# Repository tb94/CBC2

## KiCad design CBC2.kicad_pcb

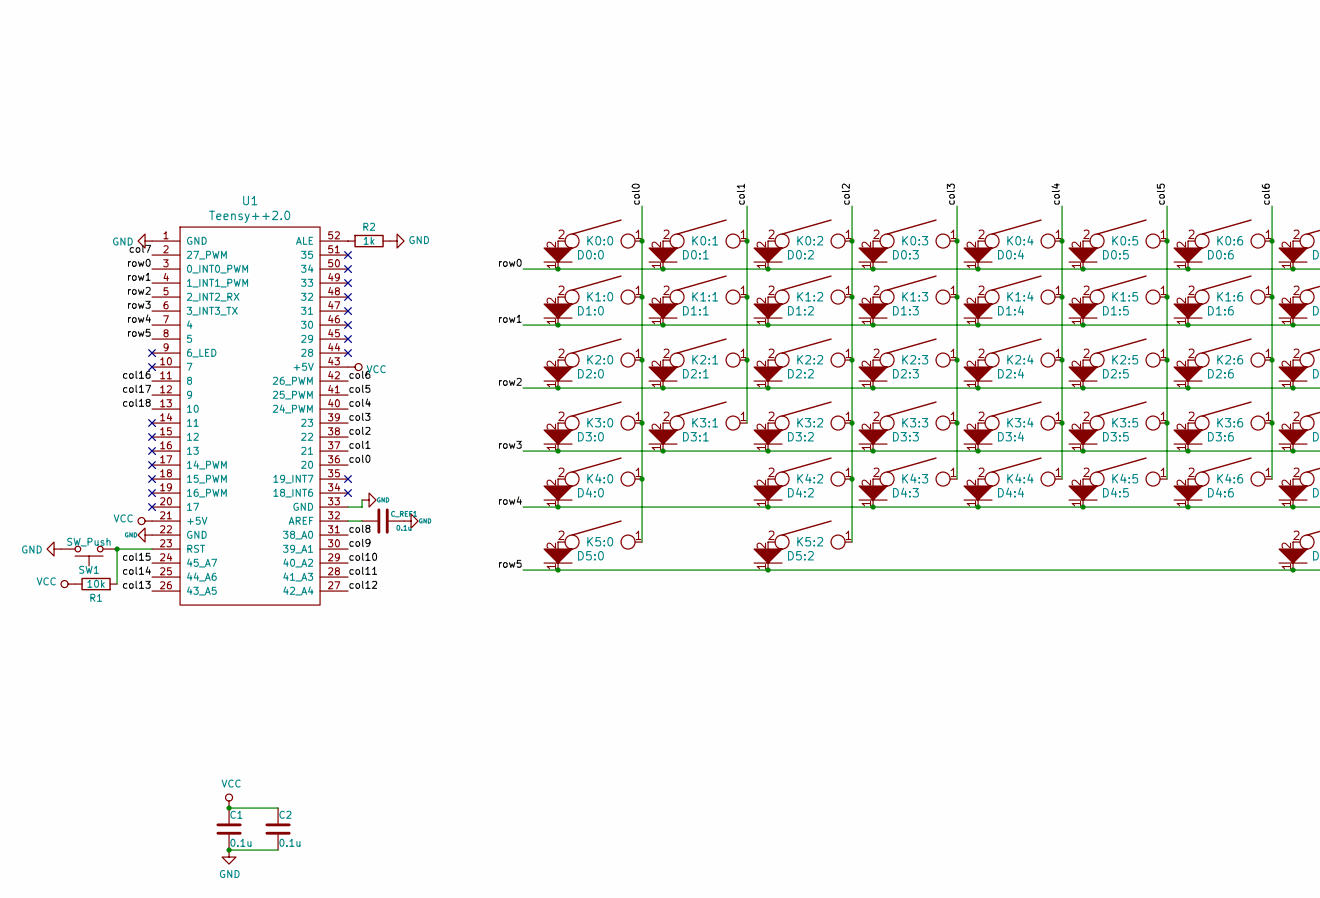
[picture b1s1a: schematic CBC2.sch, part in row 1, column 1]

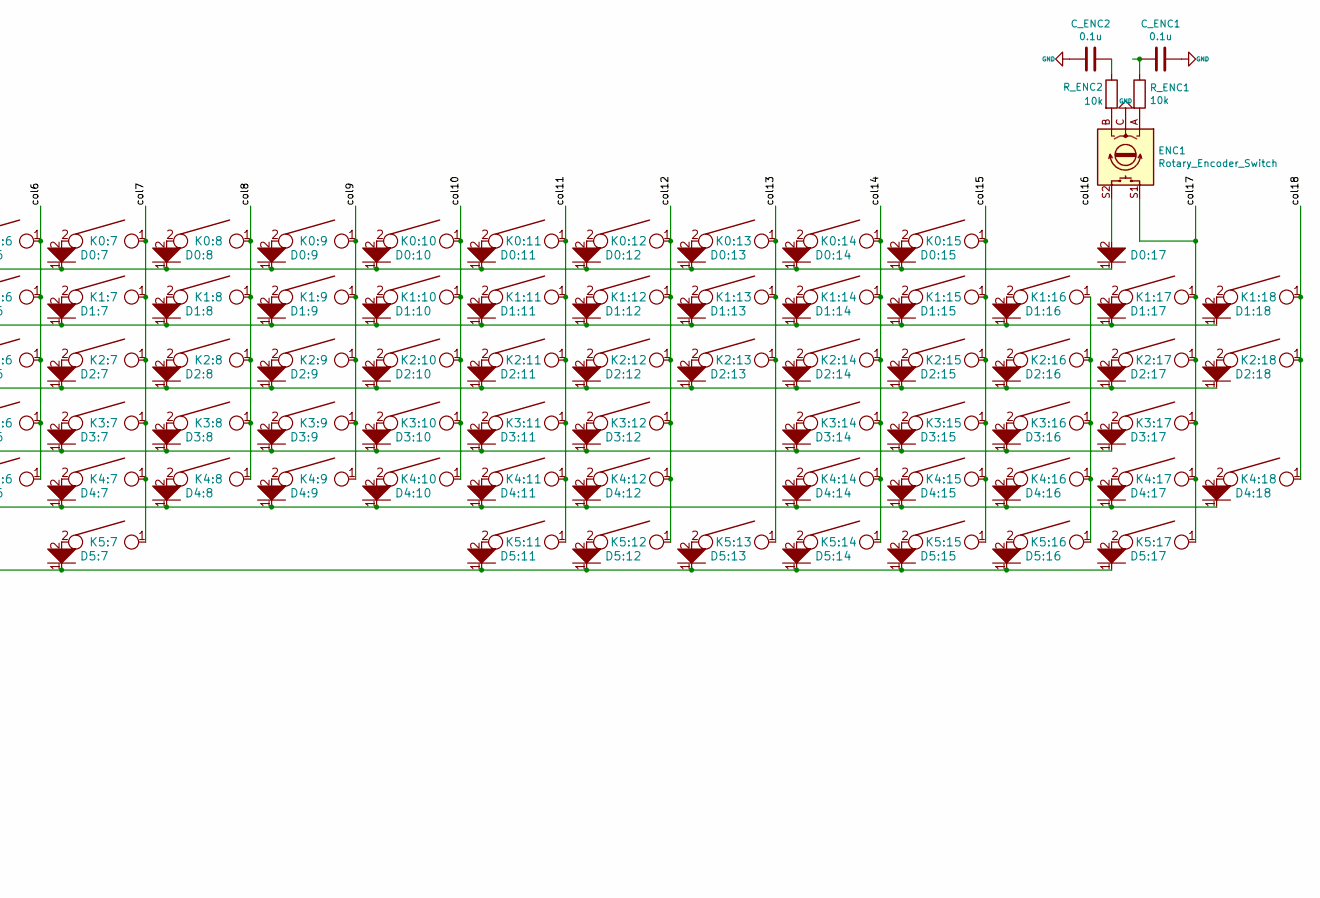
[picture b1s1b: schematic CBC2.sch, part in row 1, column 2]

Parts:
C1, C2: 0.1u; C_Axial_L3.8mm_D2.6mm_P7.50mm_Horizontal
C_ENC1, C_ENC2: 0.1u; C_Axial_L3.8mm_D2.6mm_P7.50mm_Horizontal
C_REF1: 0.1u; C_Axial_L3.8mm_D2.6mm_P7.50mm_Horizontal
D0:0, D0:1, D0:2, D0:3, D0:4, D0:5, D0:6, D0:7, D0:8, D0:9, D0:10, D0:11, D0:12, D0:13, D0:14, D0:15, D0:17, D1:0, D1:1, D1:2, D1:3, D1:4, D1:5, D1:6, D1:7, D1:8, D1:9, D1:10, D1:11, D1:12, D1:13, D1:14, D1:15, D1:16, D1:17, D1:18, D2:0, D2:1, D2:2, D2:3, D2:4, D2:5, D2:6, D2:7, D2:8, D2:9, D2:10, D2:11, D2:12, D2:13, D2:14, D2:15, D2:16, D2:17, D2:18, D3:0, D3:1, D3:2, D3:3, D3:4, D3:5, D3:6, D3:7, D3:8, D3:9, D3:10, D3:11, D3:12, D3:14, D3:15, D3:16, D3:17, D4:0, D4:2, D4:3, D4:4, D4:5, D4:6, D4:7, D4:8, D4:9, D4:10, D4:11, D4:12, D4:14, D4:15, D4:16, D4:17, D4:18, D5:0, D5:2, D5:7, D5:11, D5:12, D5:13, D5:14, D5:15, D5:16, D5:17: D; Diode-dual
ENC1: Rotary_Encoder_Switch; RotaryEncoder_Alps_EC11E-Switch_Vertical_H20mm
K0:0, K0:1, K0:2, K0:3, K0:4, K0:5, K0:6, K0:7, K0:8, K0:9, K0:10, K0:11, K0:12, K0:13, K0:14, K0:15, K1:0, K1:1, K1:2, K1:3, K1:4, K1:5, K1:6, K1:7, K1:8, K1:9, K1:10, K1:11, K1:12, K1:14, K1:15, K1:16, K1:17, K1:18, K2:1, K2:2, K2:3, K2:4, K2:5, K2:6, K2:7, K2:8, K2:9, K2:10, K2:11, K2:12, K2:14, K2:15, K2:16, K2:17, K3:1, K3:2, K3:3, K3:4, K3:5, K3:6, K3:7, K3:8, K3:9, K3:10, K3:11, K3:14, K3:15, K3:16, K3:17, K4:2, K4:3, K4:4, K4:5, K4:6, K4:7, K4:8, K4:9, K4:10, K4:11, K4:14, K4:15, K4:16, K4:17, K5:13, K5:14, K5:15, K5:16, K5:17: KEYSW; MX-1U
K1:13, K2:18, K4:18: KEYSW; MX-2U
K2:0, K2:13, K5:0, K5:2, K5:11, K5:12: KEYSW; MX-1.5U
K3:0: KEYSW; MX-1.75U
K3:12, K4:0: KEYSW; MX-2.25U
K4:12: KEYSW; MX-2.75U
K5:7: KEYSW; MX-7U
R1: 10k; R_Axial_DIN0204_L3.6mm_D1.6mm_P5.08mm_Horizontal
R2: 1k; R_Axial_DIN0204_L3.6mm_D1.6mm_P5.08mm_Horizontal
R_ENC1, R_ENC2: 10k; R_Axial_DIN0204_L3.6mm_D1.6mm_P5.08mm_Horizontal
SW1: SW_Push; SW_Tactile_SPST_Angled_MJTP1117
U1: Teensy++2.0; Teensy2.0++

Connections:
/col0: K0:0.1, K1:0.1, K2:0.1, K3:0.1, K4:0.1, K5:0.1, U1.36 (20)
/col1: K0:1.1, K1:1.1, K2:1.1, K3:1.1, U1.37 (21)
/col2: K0:2.1, K1:2.1, K2:2.1, K3:2.1, K4:2.1, K5:2.1, U1.38 (22)
/col3: K0:3.1, K1:3.1, K2:3.1, K3:3.1, K4:3.1, U1.39 (23)
/col4: K0:4.1, K1:4.1, K2:4.1, K3:4.1, K4:4.1, U1.40 (24_PWM)
/col5: K0:5.1, K1:5.1, K2:5.1, K3:5.1, K4:5.1, U1.41 (25_PWM)
/col6: K0:6.1, K1:6.1, K2:6.1, K3:6.1, K4:6.1, U1.42 (26_PWM)
/col7: K0:7.1, K1:7.1, K2:7.1, K3:7.1, K4:7.1, K5:7.1, U1.2 (27_PWM)
/col8: K0:8.1, K1:8.1, K2:8.1, K3:8.1, K4:8.1, U1.31 (38_A0)
/col9: K0:9.1, K1:9.1, K2:9.1, K3:9.1, K4:9.1, U1.30 (39_A1)
/col10: K0:10.1, K1:10.1, K2:10.1, K3:10.1, K4:10.1, U1.29 (40_A2)
/col11: K0:11.1, K1:11.1, K2:11.1, K3:11.1, K4:11.1, K5:11.1, U1.28 (41_A3)
/col12: K0:12.1, K1:12.1, K2:12.1, K3:12.1, K4:12.1, K5:12.1, U1.27 (42_A4)
/col13: K0:13.1, K1:13.1, K2:13.1, K5:13.1, U1.26 (43_A5)
/col14: K0:14.1, K1:14.1, K2:14.1, K3:14.1, K4:14.1, K5:14.1, U1.25 (44_A6)
/col15: K0:15.1, K1:15.1, K2:15.1, K3:15.1, K4:15.1, K5:15.1, U1.24 (45_A7)
/col16: U1.11 (8)
/col17: ENC1.S1, K1:17.1, K2:17.1, K3:17.1, K4:17.1, K5:17.1, U1.12 (9)
/col18: K1:18.1, K2:18.1, K4:18.1, U1.13 (10)
/row0: D0:0.1, D0:1.1, D0:2.1, D0:3.1, D0:4.1, D0:5.1, D0:6.1, D0:7.1, D0:8.1, D0:9.1, D0:10.1, D0:11.1, D0:12.1, D0:13.1, D0:14.1, D0:15.1, D0:17.1, U1.3 (0_INT0_PWM)
/row1: D1:0.1, D1:1.1, D1:2.1, D1:3.1, D1:4.1, D1:5.1, D1:6.1, D1:7.1, D1:8.1, D1:9.1, D1:10.1, D1:11.1, D1:12.1, D1:13.1, D1:14.1, D1:15.1, D1:16.1, D1:17.1, D1:18.1, U1.4 (1_INT1_PWM)
/row2: D2:0.1, D2:1.1, D2:2.1, D2:3.1, D2:4.1, D2:5.1, D2:6.1, D2:7.1, D2:8.1, D2:9.1, D2:10.1, D2:11.1, D2:12.1, D2:13.1, D2:14.1, D2:15.1, D2:16.1, D2:17.1, D2:18.1, U1.5 (2_INT2_RX)
/row3: D3:0.1, D3:1.1, D3:2.1, D3:3.1, D3:4.1, D3:5.1, D3:6.1, D3:7.1, D3:8.1, D3:9.1, D3:10.1, D3:11.1, D3:12.1, D3:14.1, D3:15.1, D3:16.1, D3:17.1, U1.6 (3_INT3_TX)
/row4: D4:0.1, D4:2.1, D4:3.1, D4:4.1, D4:5.1, D4:6.1, D4:7.1, D4:8.1, D4:9.1, D4:10.1, D4:11.1, D4:12.1, D4:14.1, D4:15.1, D4:16.1, D4:17.1, D4:18.1, U1.7 (4)
/row5: D5:0.1, D5:2.1, D5:7.1, D5:11.1, D5:12.1, D5:13.1, D5:14.1, D5:15.1, D5:16.1, D5:17.1, U1.8 (5)
GND: C1.2, C2.2, C_ENC1.1, C_ENC2.2, C_REF1.1, ENC1.C, R2.1, SW1.2, U1.1 (GND), U1.22 (GND), U1.33 (GND)
unnamed: C_ENC1.2, R_ENC1.1
unnamed: C_ENC2.1, R_ENC2.1
unnamed: C_REF1.2, U1.32 (AREF)
unnamed: D0:0.2, K0:0.2
unnamed: D0:1.2, K0:1.2
unnamed: D0:2.2, K0:2.2
unnamed: D0:3.2, K0:3.2
unnamed: D0:4.2, K0:4.2
unnamed: D0:5.2, K0:5.2
unnamed: D0:6.2, K0:6.2
unnamed: D0:7.2, K0:7.2
unnamed: D0:8.2, K0:8.2
unnamed: D0:9.2, K0:9.2
unnamed: D0:10.2, K0:10.2
unnamed: D0:11.2, K0:11.2
unnamed: D0:12.2, K0:12.2
unnamed: D0:13.2, K0:13.2
unnamed: D0:14.2, K0:14.2
unnamed: D0:15.2, K0:15.2
unnamed: D0:17.2, ENC1.S2
unnamed: D1:0.2, K1:0.2
unnamed: D1:1.2, K1:1.2
unnamed: D1:2.2, K1:2.2
unnamed: D1:3.2, K1:3.2
unnamed: D1:4.2, K1:4.2
unnamed: D1:5.2, K1:5.2
unnamed: D1:6.2, K1:6.2
unnamed: D1:7.2, K1:7.2
unnamed: D1:8.2, K1:8.2
unnamed: D1:9.2, K1:9.2
unnamed: D1:10.2, K1:10.2
unnamed: D1:11.2, K1:11.2
unnamed: D1:12.2, K1:12.2
unnamed: D1:13.2, K1:13.2
unnamed: D1:14.2, K1:14.2
unnamed: D1:15.2, K1:15.2
unnamed: D1:16.2, K1:16.2
unnamed: D1:17.2, K1:17.2
unnamed: D1:18.2, K1:18.2
unnamed: D2:0.2, K2:0.2
unnamed: D2:1.2, K2:1.2
unnamed: D2:2.2, K2:2.2
unnamed: D2:3.2, K2:3.2
unnamed: D2:4.2, K2:4.2
unnamed: D2:5.2, K2:5.2
unnamed: D2:6.2, K2:6.2
unnamed: D2:7.2, K2:7.2
unnamed: D2:8.2, K2:8.2
unnamed: D2:9.2, K2:9.2
unnamed: D2:10.2, K2:10.2
unnamed: D2:11.2, K2:11.2
unnamed: D2:12.2, K2:12.2
unnamed: D2:13.2, K2:13.2
unnamed: D2:14.2, K2:14.2
unnamed: D2:15.2, K2:15.2
unnamed: D2:16.2, K2:16.2
unnamed: D2:17.2, K2:17.2
unnamed: D2:18.2, K2:18.2
unnamed: D3:0.2, K3:0.2
unnamed: D3:1.2, K3:1.2
unnamed: D3:2.2, K3:2.2
unnamed: D3:3.2, K3:3.2
unnamed: D3:4.2, K3:4.2
unnamed: D3:5.2, K3:5.2
unnamed: D3:6.2, K3:6.2
unnamed: D3:7.2, K3:7.2
unnamed: D3:8.2, K3:8.2
unnamed: D3:9.2, K3:9.2
unnamed: D3:10.2, K3:10.2
unnamed: D3:11.2, K3:11.2
unnamed: D3:12.2, K3:12.2
unnamed: D3:14.2, K3:14.2
unnamed: D3:15.2, K3:15.2
unnamed: D3:16.2, K3:16.2
unnamed: D3:17.2, K3:17.2
unnamed: D4:0.2, K4:0.2
unnamed: D4:2.2, K4:2.2
unnamed: D4:3.2, K4:3.2
unnamed: D4:4.2, K4:4.2
unnamed: D4:5.2, K4:5.2
unnamed: D4:6.2, K4:6.2
unnamed: D4:7.2, K4:7.2
unnamed: D4:8.2, K4:8.2
unnamed: D4:9.2, K4:9.2
unnamed: D4:10.2, K4:10.2
unnamed: D4:11.2, K4:11.2
unnamed: D4:12.2, K4:12.2
unnamed: D4:14.2, K4:14.2
unnamed: D4:15.2, K4:15.2
unnamed: D4:16.2, K4:16.2
unnamed: D4:17.2, K4:17.2
unnamed: D4:18.2, K4:18.2
unnamed: D5:0.2, K5:0.2
unnamed: D5:2.2, K5:2.2
unnamed: D5:7.2, K5:7.2
unnamed: D5:11.2, K5:11.2
unnamed: D5:12.2, K5:12.2
unnamed: D5:13.2, K5:13.2
unnamed: D5:14.2, K5:14.2
unnamed: D5:15.2, K5:15.2
unnamed: D5:16.2, K5:16.2
unnamed: D5:17.2, K5:17.2
unnamed: ENC1.A, R_ENC1.2
unnamed: ENC1.B, R_ENC2.2
unnamed: K1:16.1, K2:16.1, K3:16.1, K4:16.1, K5:16.1
unnamed: R1.2, SW1.1, U1.23 (RST)
unnamed: R2.2, U1.52 (ALE)
VCC: C1.1, C2.1, R1.1, U1.21 (+5V), U1.43 (+5V)

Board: 2 copper layers, 209 parts (110 on the bottom side), 133 nets, no tracks yet.

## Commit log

2019-04-04 finished schematics
2019-04-04 started pcb layout. teensy footprint needs adjustments, or install teensy library and replace symbol
2019-04-05 added teensy symbol library to replace broken symbol and remapped connections
2019-04-05 layed out the switch matrix
2019-04-06 finished layout. still needs adjustments to schematics to reflect layout
2019-04-07 switched to keeb.io library and placed diodes
2019-04-09 fixed +5v vs GND discrepency. More routing.
2019-04-09 almost done routing. still needs DRC
2019-04-10 final touches
2019-04-17 i lied. started the pcb from scratch after modifying schematic and layout plans
2019-05-05 updated footprints for layout adjustment. placed diodes, still on the fence about the microcontroller placement
